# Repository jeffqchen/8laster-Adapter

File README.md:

# 8laster Adapter for Krikzz's RGB Blaster

Krikzz's [RGB Blaster](https://krikzz.com/our-products/cartridges/rgb-blaster.html) is an innovative way to achieve RGB video output on an unmodded Famicom console.

However, the initial batch of the RGB Blaster had several issues. Krikzz posted some fix, but eventually it will be re-designed and re-released with a new revision.

For the initial batch units, we not only need to apply the [suggested fix](https://twitter.com/krikzz/status/1605908227190833153), but also it seems the video DAC chip [ADV7123](https://www.analog.com/en/products/adv7123.html) is not suitable to work with a 9-pin mini DIN RGBS SCART standard cable. Instead, the 8-pin mini DIN "XRGB Mini" standard, which is also used on the NESRGB and 3DORGB, seems to be a better one. Therefore, I created this 9-pin mini DIN to 8-pin mini DIN adapter called the "8laster".

The 8laster works with my own [8DIN2VGA adapter](https://github.com/jeffqchen/8DIN2VGA) and has almost all the Famicom consoles in consideration (yeah, I don't have the titler.)

Of course, it works with any 8-pin mini DIN SCART cable, for example, the one you can purchase with the NESRGB.

## Tech Details

The 8laster adds another set of 150 ohm resistors (R1-R3) to GND on the RGB line, restoring them back to the standard 75 ohm terminated standard.

It offers the option to add the attenuation resistor (R4) on the adapter instead of the RGB Blaster itself. The value 150 plus the original internal 47R is close enough to the suggested 220R (If you insist having the exact value, 173 Ohm would be the proper value).

However, if you've **ALREADY** applied the suggested fixes, you must close J1 with a solder blob.

Regarding the suggested fix on the 680R resistor, if you don't feel confident removing the original 680R resistor, you can add a 1.5K Ohm one piggy-backing onto the original one to achieve the intended 470R.

### Going Completely Stock?

If you did NOT apply any of the suggested fixes, with a properly configured 8laster, you will get a proper image, just slightly darker than optimal.

## Parts

- [8laster PCB](https://oshpark.com/projects/GstOPotZ)

- 3D-printed shells
  - [Front](https://github.com/jeffqchen/8laster-Adapter/blob/main/3D%20Print/Front%20Shell.stl)
  - [Back](https://github.com/jeffqchen/8laster-Adapter/blob/main/3D%20Print/Back%20Shell.stl)

- 9 pin Mini DIN Male Plug, Through-Hole Type - [Link](https://github.com/jeffqchen/JeffParts/blob/main/Connectors/Mini%20DIN/9Pin/Through%20Hole/info.md)

- 8-pin mini DIN Female Socket (widely available from various sources)

- M3x8mm screw and nut - [Link](https://github.com/jeffqchen/JeffParts/blob/main/Parts/M2%20M3%20Hex%20Screw%20%26%20Nut/info.md)

- [4x] SMD resistors, Imperial size 0603, 150 Ohm for R1-R4

## 3D Print
Print the shells as indicated in the picture, with support.

## Assembly

First, populate the SMD R1-R4 on the PCB. Short J1 if the suggested fixes were already applied.

Second, slightly spread the shield pins on the two sides of the 8-pin mini DIN female socket. Then insert it **all the way** into the PCB, from the "Outside" side (pins should protrude from the "Inside" side). Solder the shield pins one by one, while making sure the socket remains as flush as possible to the PCB. Then, proceed to solder the rest of the pins.

Then, insert the 8-pin mini DIN male plug from the "Inside" side. Make sure it's flush to the PCB as wel, the solder in the shield pin on top. Proceed to solder the rest of the pins while making sure it's flush to the PCB.

Fit the soldered assembly into the shells and close up with the M3x8mm screw and nut.

Note the nut is on the 8DIN side and the screw is on the 9DIN side.

-----
Shield: [![CC BY-SA 4.0][cc-by-sa-shield]][cc-by-sa]

This work is licensed under a
[Creative Commons Attribution-ShareAlike 4.0 International License][cc-by-sa].

[![CC BY-SA 4.0][cc-by-sa-image]][cc-by-sa]

[cc-by-sa]: http://creativecommons.org/licenses/by-sa/4.0/
[cc-by-sa-image]: https://licensebuttons.net/l/by-sa/4.0/88x31.png
[cc-by-sa-shield]: https://img.shields.io/badge/License-CC%20BY--SA%204.0-lightgrey.svg

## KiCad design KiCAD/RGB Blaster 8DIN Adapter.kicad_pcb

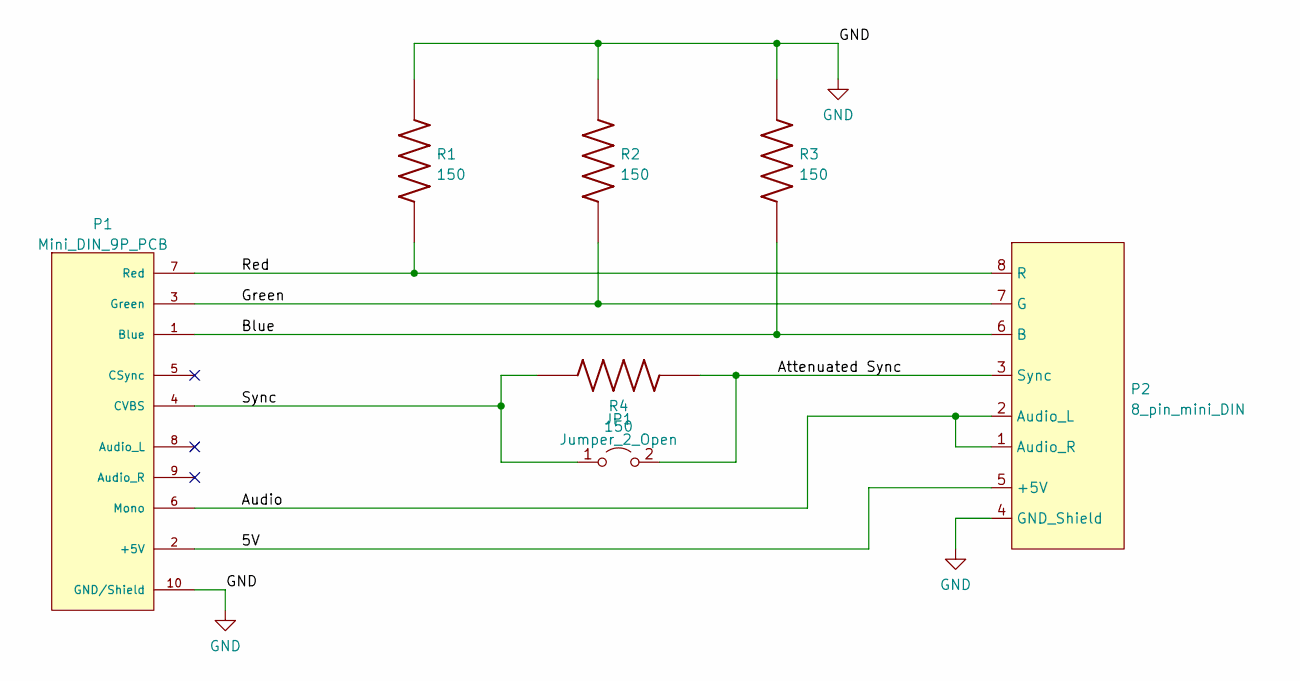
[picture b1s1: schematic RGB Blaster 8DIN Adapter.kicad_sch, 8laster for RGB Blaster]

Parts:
JP1: Jumper_2_Open; SolderJumper-2_P1.3mm_Open_TrianglePad1.0x1.5mm
P1: Mini_DIN_9P_PCB; 9 pin mini DIN PCB
P2: 8_pin_mini_DIN; 8 pin mini DIN
R1, R2, R3, R4: 150; R_0603_1608Metric_Pad0.98x0.95mm_HandSolder

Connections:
/5V: P1.2 (+5V), P2.5 (+5V)
/Attenuated Sync: JP1.2 (B), P2.3 (Sync), R4.2
/Audio: P1.6 (Mono), P2.1 (Audio_R), P2.2 (Audio_L)
/Blue: P1.1 (Blue), P2.6 (B), R3.1
/Green: P1.3 (Green), P2.7 (G), R2.1
/Red: P1.7 (Red), P2.8 (R), R1.1
/Sync: JP1.1 (A), P1.4 (CVBS), R4.1
GND: P1.10 (GND/Shield), P2.4 (GND_Shield), R1.2, R2.2, R3.2

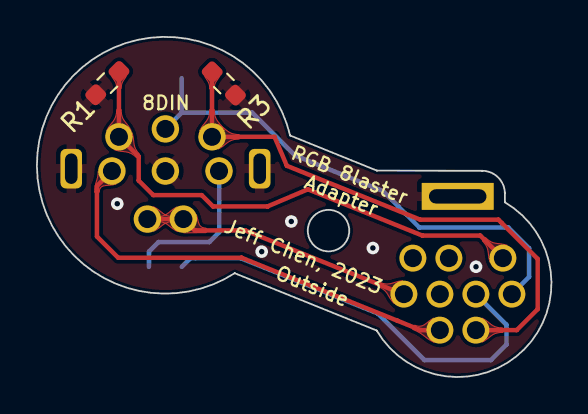
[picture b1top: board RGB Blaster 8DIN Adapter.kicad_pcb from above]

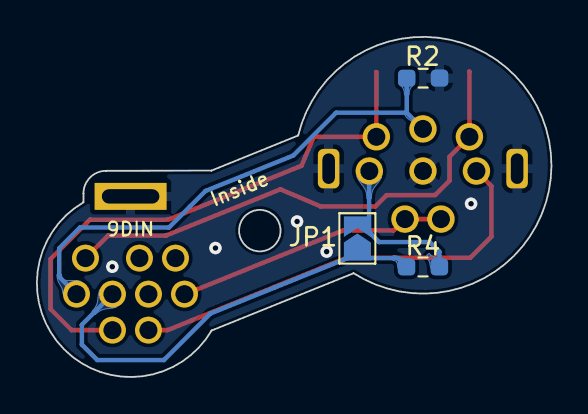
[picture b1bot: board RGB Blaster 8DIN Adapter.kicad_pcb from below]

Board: 2 copper layers, 28.6 x 18.9 mm, 7 parts (4 on the bottom side), 8 nets.

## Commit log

2023-01-29 Initial Upload
2023-01-29 Changes on KiCAD project
